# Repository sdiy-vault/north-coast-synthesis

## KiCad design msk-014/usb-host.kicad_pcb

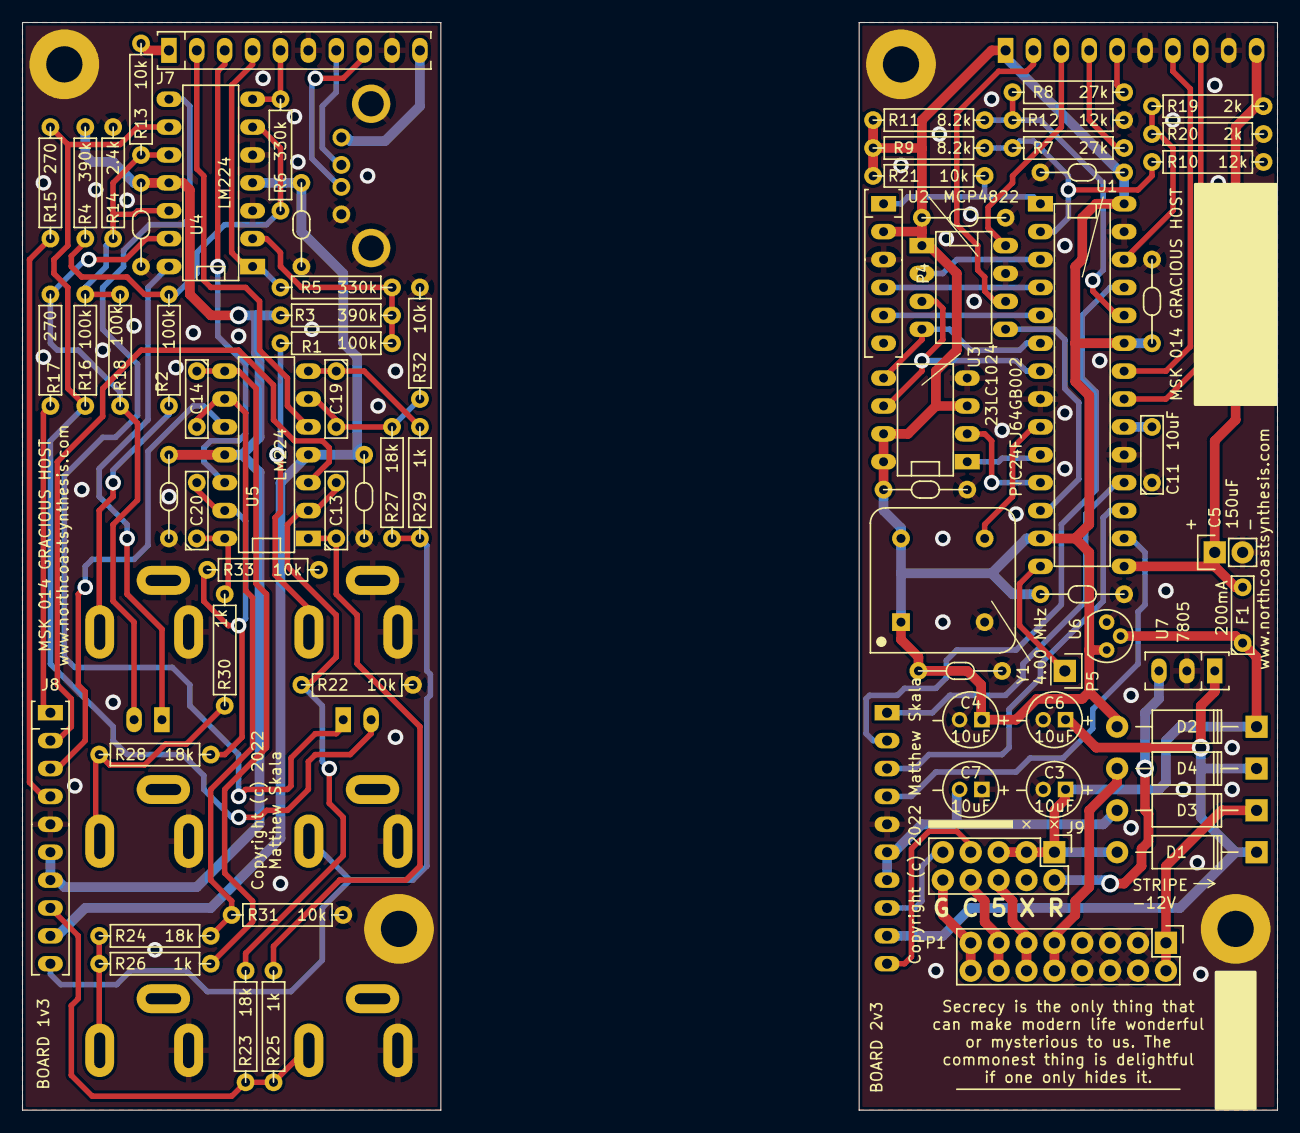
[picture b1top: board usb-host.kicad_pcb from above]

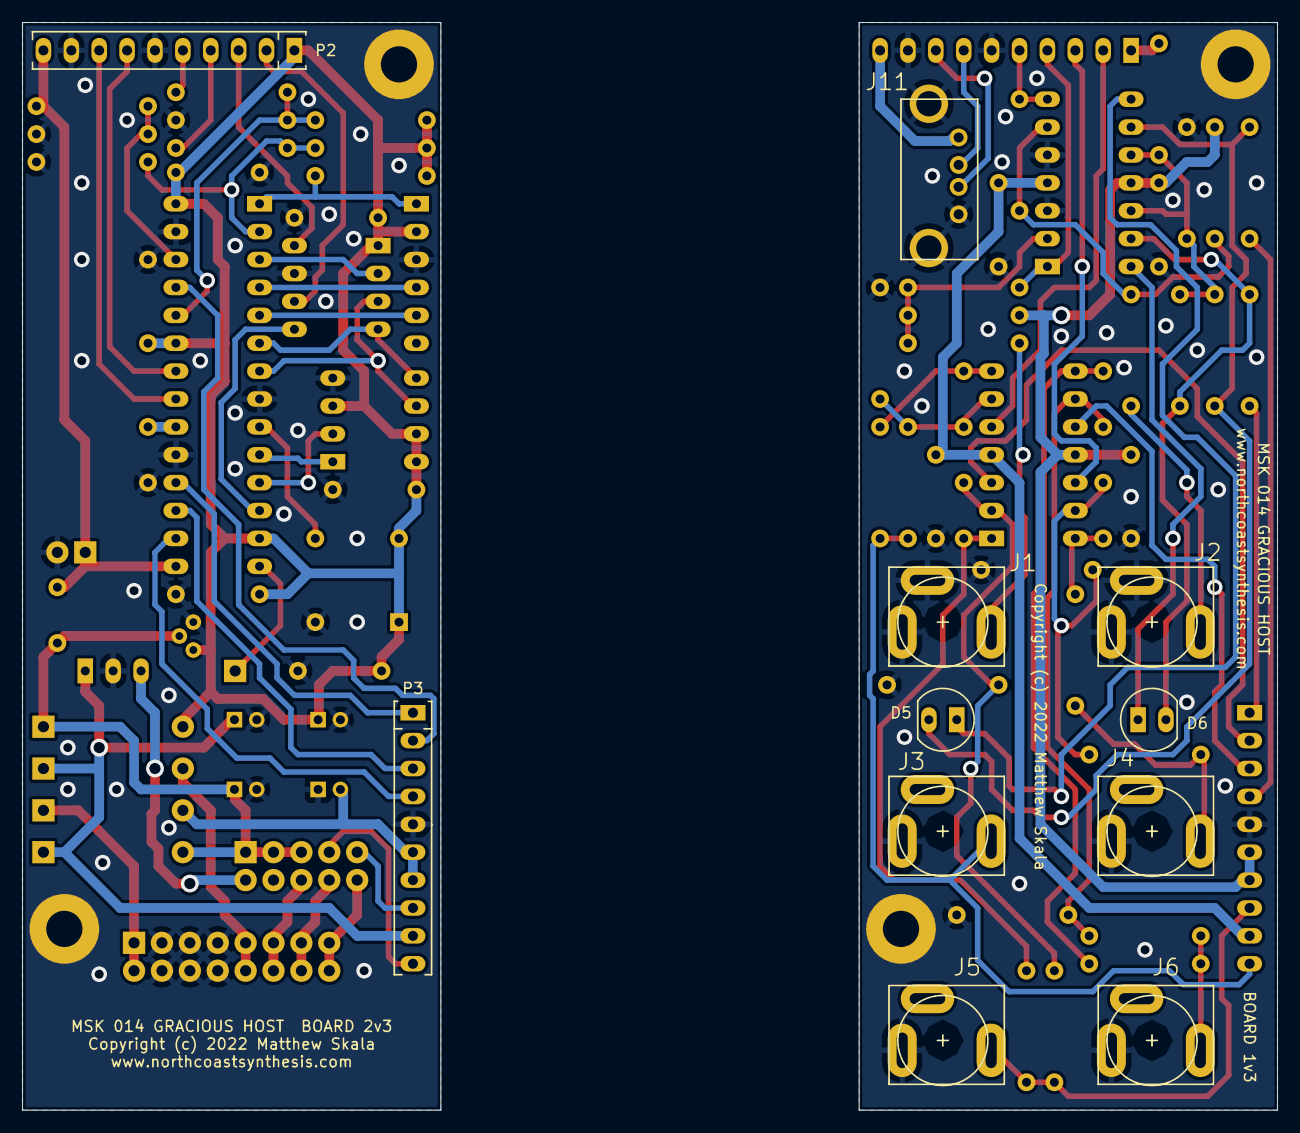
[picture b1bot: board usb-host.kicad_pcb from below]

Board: 2 copper layers, 114.3 x 99.1 mm, 87 parts (11 on the bottom side), 58 nets.

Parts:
C1, C2, C8, C9, C10, C12, C15, C16, C17, C18: 0.1uF; C3msk
C3, C4, C6, C7: 10uF; C08msk
C5: 150uF; 1x02msk
C11: 10uF; C2msk
C13, C14, C19, C20: 100pF; C2msk
D1, D2, D3, D4: 1N5818; DO15msk
D5, D6: MCL056PURGW; LEDmsk
F1: 200mA; C2msk
H1, H2, H3, H4: CONN_01X01; MountingHole_M3
J1, J2, J3, J4, J5, J6: JACK_2P; mono_jack_slotted
J7, J8: CONN_01X10; SIP10-socket
J9: CONN_02X05; 2x05msk
J11: USB_A; USB_A_vert
P1: Conn_02x08_Odd_Even; 2x08ra
P2, P3: CONN_01X10; SIP10-pins
P4: Conn_01x06; SIP6msk
P5: CONN_01X01; 1x01msk
R1, R2, R16, R18: 100k; R4valmsk
R3, R4: 390k; R4valmsk
R5, R6: 330k; R4valmsk
R7, R8: 27k; R4valmsk
R9, R11: 8.2k; R4valmsk
R10, R12: 12k; R4valmsk
R13, R21, R22, R31, R32, R33: 10k; R4valmsk
R14: 2.4k; R4valmsk
R15, R17: 270; R4valmsk
R19, R20: 2k; R4valmsk
R23, R24, R27, R28: 18k; R4valmsk
R25, R26, R29, R30: 1k; R4valmsk
U1: PIC24FJ64GB002; SDIP28_clipped
U2: MCP4822; DIP08msk
U3: 23LC1024; DIP08msk
U4, U5: LM224; DIP14msk_clipped
U6: MCP1700-3302; TO92msk
U7: 7805; SIP3msk
Y1: 4.00 MHz; DIP08_xtal

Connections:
+3.3V: C4.1, C8.2, C9.2, C10.2, C12.2, C15.2, C16.2, D2.1 (A), J7.1, P2.1, P4.2, R9.1, R11.1, R13.1, R21.1, U1.13 (Vdd), U1.23 (Vusb), U1.28 (Vdd), U2.1 (Vdd), U3.3 (SIO2), U3.7 (~HOLD), U3.8 (Vcc), U6.3 (VO), Y1.1 (EN), Y1.8 (Vcc)
+5V: C3.1, D1.1 (A), D2.2 (K), F1.1, J9.1, J9.3, J9.5, U6.2 (VI)
+12V: C2.1, C6.1, C18.1, D1.2 (K), D4.2 (K), J8.9, P3.9, U4.4 (V+), U5.4 (V+), U7.1 (IN)
-12V: C1.1, C7.2, C17.1, D3.1 (A), J8.6, J8.7, P3.6, P3.7, R3.2, R4.2, U4.11 (V-), U5.11 (V-)
/CV1: J7.2, P2.2, U2.6 (VB), U5.5 (+)
/CV2: J7.3, P2.3, U2.8 (VA), U5.12 (+)
/D+: J7.8, J11.3 (D+), P2.8, U1.21 (D+)
/D-: J7.7, J11.2 (D-), P2.7, U1.22 (D-)
/DOUT1: J8.2, P3.2, U1.25 (DOUT1), U5.3 (+)
/DOUT2: J8.3, P3.3, U1.17 (DOUT2), U5.10 (+)
/G1: J5.1, J8.8, J9.9, P3.8, R23.2, R25.2
/LED1: J8.4, P3.4, R15.2, U1.16 (LED1)
/LED2: J8.1, P3.1, R17.2, U1.18 (LED2)
/Vbus: C5.1, F1.2, J7.10, J11.1 (VBUS), P2.10, R19.2, U1.15 (Vbus)
/XCV1: J3.1, J8.10, J9.7, P3.10, R27.2, R29.2
/XIN1: J7.4, P2.4, R5.1, R7.2, U4.1
/XIN2: J7.5, P2.5, R6.1, R8.2, U4.7
GNDREF: C1.2, C2.2, C3.2, C4.2, C5.2, C6.2, C7.1, C8.1, C9.1, C10.1, C11.1, C12.1, C15.1, C16.1, C17.2, C18.2, H1.1, H2.1, H3.1, H4.1, J1.2, J1.3, J2.2, J2.3, J3.3, J4.3, J5.3, J6.3, J7.6, J7.9, J8.5, J11.4 (GND), J11.5 (Shield), P1.3, P1.4, P1.5, P1.6, P1.7, P1.8, P2.6, P2.9, P3.5, P4.3, R10.2, R12.2, R14.2, R20.2, R22.1, R31.1, R32.1, R33.1, U1.8 (Vss), U1.19 (DISVREG), U1.27 (Vss), U2.7 (Vss), U3.4 (Vss), U4.3 (+), U4.5 (+), U6.1 (GND), U7.2 (GND), Y1.4 (GND)
unnamed: C11.2, U1.20 (Vcap)
unnamed: C13.1, R25.1, U5.1
unnamed: C13.2, R22.2, R23.1, U5.2 (-)
unnamed: C14.1, R26.1, U5.8
unnamed: C14.2, R24.1, R31.2, U5.9 (-)
unnamed: C19.1, R29.1, U5.7
unnamed: C19.2, R27.1, R32.2, U5.6 (-)
unnamed: C20.1, R30.1, U5.14
unnamed: C20.2, R28.1, R33.2, U5.13 (-)
unnamed: D3.2 (K), P1.1, P1.2
unnamed: D4.1 (A), P1.9, P1.10
unnamed: D5.1 (A), R15.1, R16.1, U4.9 (-)
unnamed: D5.2 (K), U4.8
unnamed: D6.1 (A), R17.1, R18.1, U4.13 (-)
unnamed: D6.2 (K), U4.14
unnamed: J1.1, R1.2
unnamed: J2.1, R2.2
unnamed: J4.1, R28.2, R30.2
unnamed: J6.1, R24.2, R26.2
unnamed: J9.2, U7.3 (OUT)
unnamed: J9.6, P1.11, P1.12
unnamed: J9.8, P1.13, P1.14
unnamed: J9.10, P1.15, P1.16
unnamed: P4.1, R21.2, U1.1 (~MCLR)
unnamed: P4.4, U1.4 (PGED1)
unnamed: P4.5, U1.5 (PGEC1)
unnamed: P5.1, U1.14 (RB5)
unnamed: R1.1, R3.1, R5.2, U4.2 (-)
unnamed: R2.1, R4.1, R6.2, U4.6 (-)
unnamed: R7.1, R9.2, R10.1, U1.2 (DIN1)
unnamed: R8.1, R11.2, R12.1, U1.24 (DIN2)
unnamed: R13.2, R14.1, R16.2, R18.2, U4.10 (+), U4.12 (+)
unnamed: R19.1, R20.1, U1.26 (AN9)
unnamed: U1.3 (~CS1), U2.2 (~CS)
unnamed: U1.6 (SDO), U2.4 (SDI), U3.5 (SDI)
unnamed: U1.7 (SCK), U2.3 (SCK), U3.6 (SCK)
unnamed: U1.9 (OSCI), Y1.5 (OUT)
unnamed: U1.10 (~CS2), U3.1 (~CS)
unnamed: U1.11 (SDI), U3.2 (SDO)
unnamed: U1.12 (~LDAC), U2.5 (~LDAC)

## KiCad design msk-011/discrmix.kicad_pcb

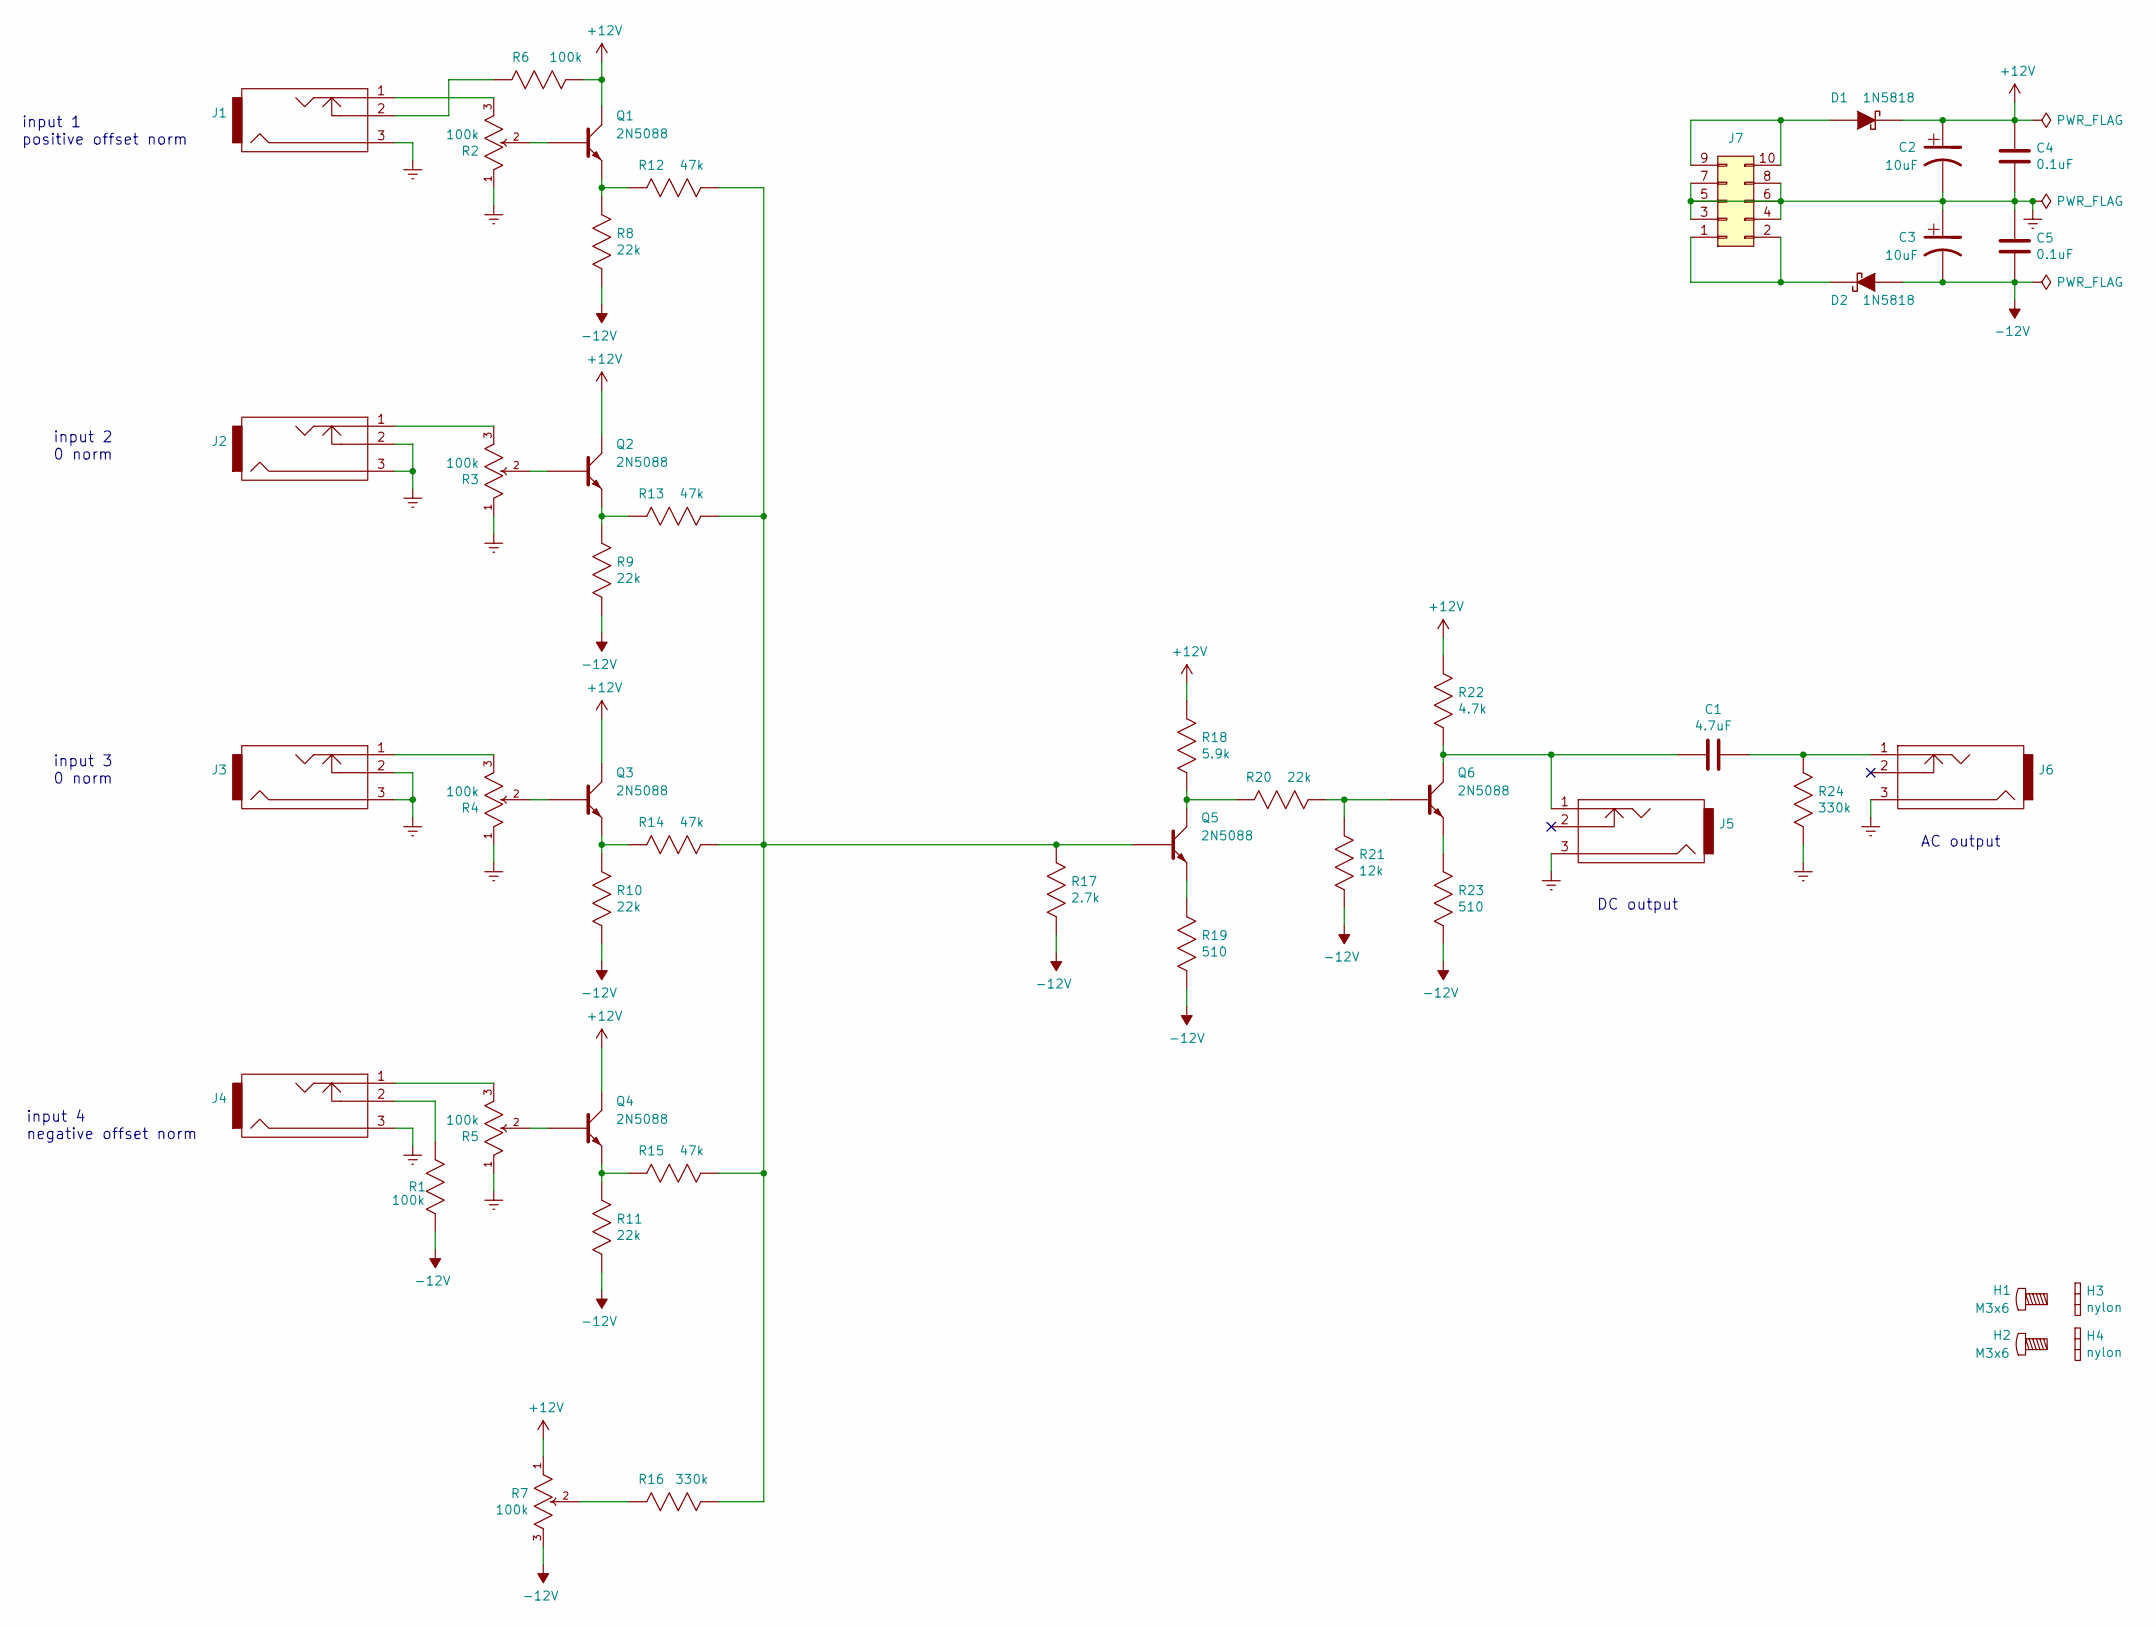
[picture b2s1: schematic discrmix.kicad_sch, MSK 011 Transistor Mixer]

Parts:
C1: 4.7uF; C2_3x2msk
C2, C3: 10uF; C1V7msk
C4, C5: 0.1uF; C3msk
D1, D2: 1N5818; DO15msk
H1, H2: M3x6; Hardware
H3, H4: nylon; Hardware
J1, J2, J3, J4, J5, J6: JACK_2P; jack_ra_slotted_msk
J7: CONN_02X05; 2x05msk
Q1, Q2, Q3, Q4, Q5, Q6: 2N5088; TO92msk
R1, R6: 100k; R4valmsk
R2, R3, R4, R5: 100k; 260Pmsk
R7: 100k; 3386Pmsk
R8, R9, R10, R11, R20: 22k; R4valmsk
R12, R13, R14, R15: 47k; R4valmsk
R16, R24: 330k; R4valmsk
R17: 2.7k; R4valmsk
R18: 5.9k; R4valmsk
R19, R23: 510; R4valmsk
R21: 12k; R4valmsk
R22: 4.7k; R4valmsk

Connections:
+12V: C2.1, C4.1, D1.2 (K), Q1.3 (C), Q2.3 (C), Q3.3 (C), Q4.3 (C), R6.2, R7.1, R18.1, R22.1
-12V: C3.2, C5.2, D2.1 (A), R1.2, R7.3, R8.2, R9.2, R10.2, R11.2, R17.2, R19.2, R21.2, R23.2
GNDREF: C2.2, C3.1, C4.2, C5.1, J1.3, J2.2, J2.3, J3.2, J3.3, J4.3, J5.3, J6.3, J7.3, J7.4, J7.5, J7.6, J7.7, J7.8, R2.1, R3.1, R4.1, R5.1, R24.2
unnamed: C1.1, J6.1, R24.1
unnamed: C1.2, J5.1, Q6.3 (C), R22.2
unnamed: D1.1 (A), J7.9, J7.10
unnamed: D2.2 (K), J7.1, J7.2
unnamed: J1.1, R2.3
unnamed: J1.2, R6.1
unnamed: J2.1, R3.3
unnamed: J3.1, R4.3
unnamed: J4.1, R5.3
unnamed: J4.2, R1.1
unnamed: Q1.1 (E), R8.1, R12.1
unnamed: Q1.2 (B), R2.2
unnamed: Q2.1 (E), R9.1, R13.1
unnamed: Q2.2 (B), R3.2
unnamed: Q3.1 (E), R10.1, R14.1
unnamed: Q3.2 (B), R4.2
unnamed: Q4.1 (E), R11.1, R15.1
unnamed: Q4.2 (B), R5.2
unnamed: Q5.1 (E), R19.1
unnamed: Q5.2 (B), R12.2, R13.2, R14.2, R15.2, R16.2, R17.1
unnamed: Q5.3 (C), R18.2, R20.1
unnamed: Q6.1 (E), R23.1
unnamed: Q6.2 (B), R20.2, R21.1
unnamed: R7.2, R16.1

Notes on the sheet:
DC output
AC output
input 3 0 norm
input 1 positive offset norm
input 4 negative offset norm
input 2 0 norm

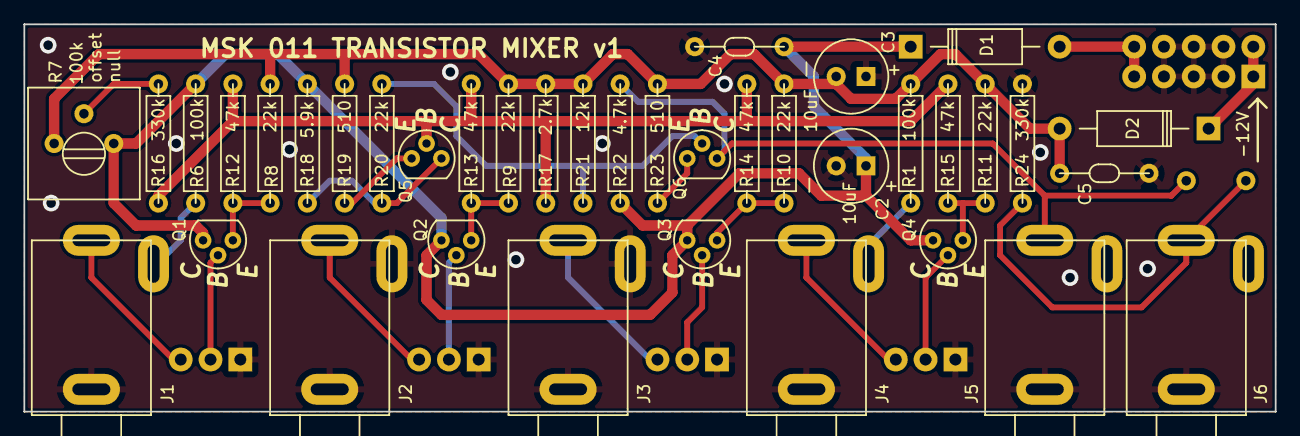
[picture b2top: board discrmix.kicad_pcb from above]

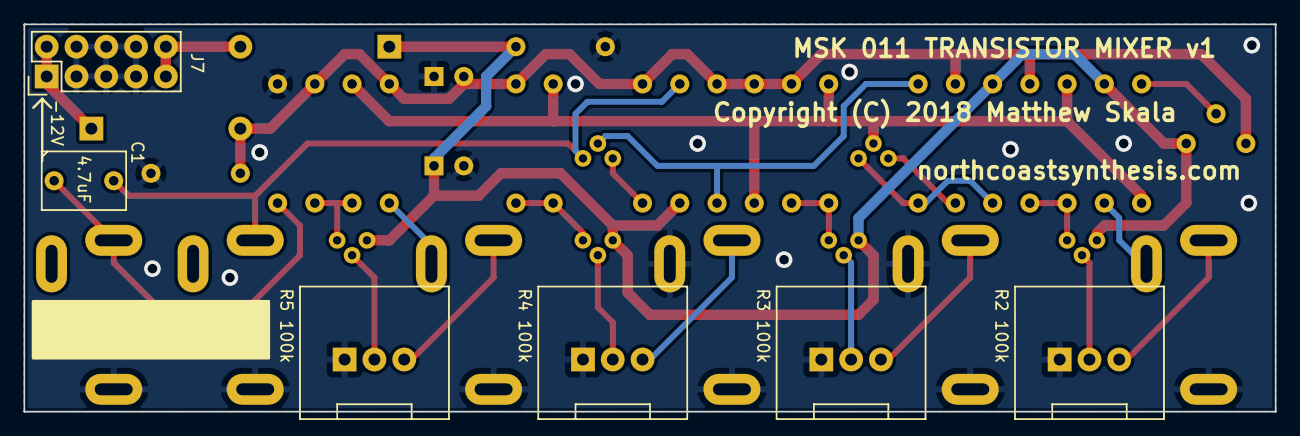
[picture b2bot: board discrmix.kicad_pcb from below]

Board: 2 copper layers, 106.7 x 33.0 mm, 44 parts (6 on the bottom side), 27 nets.

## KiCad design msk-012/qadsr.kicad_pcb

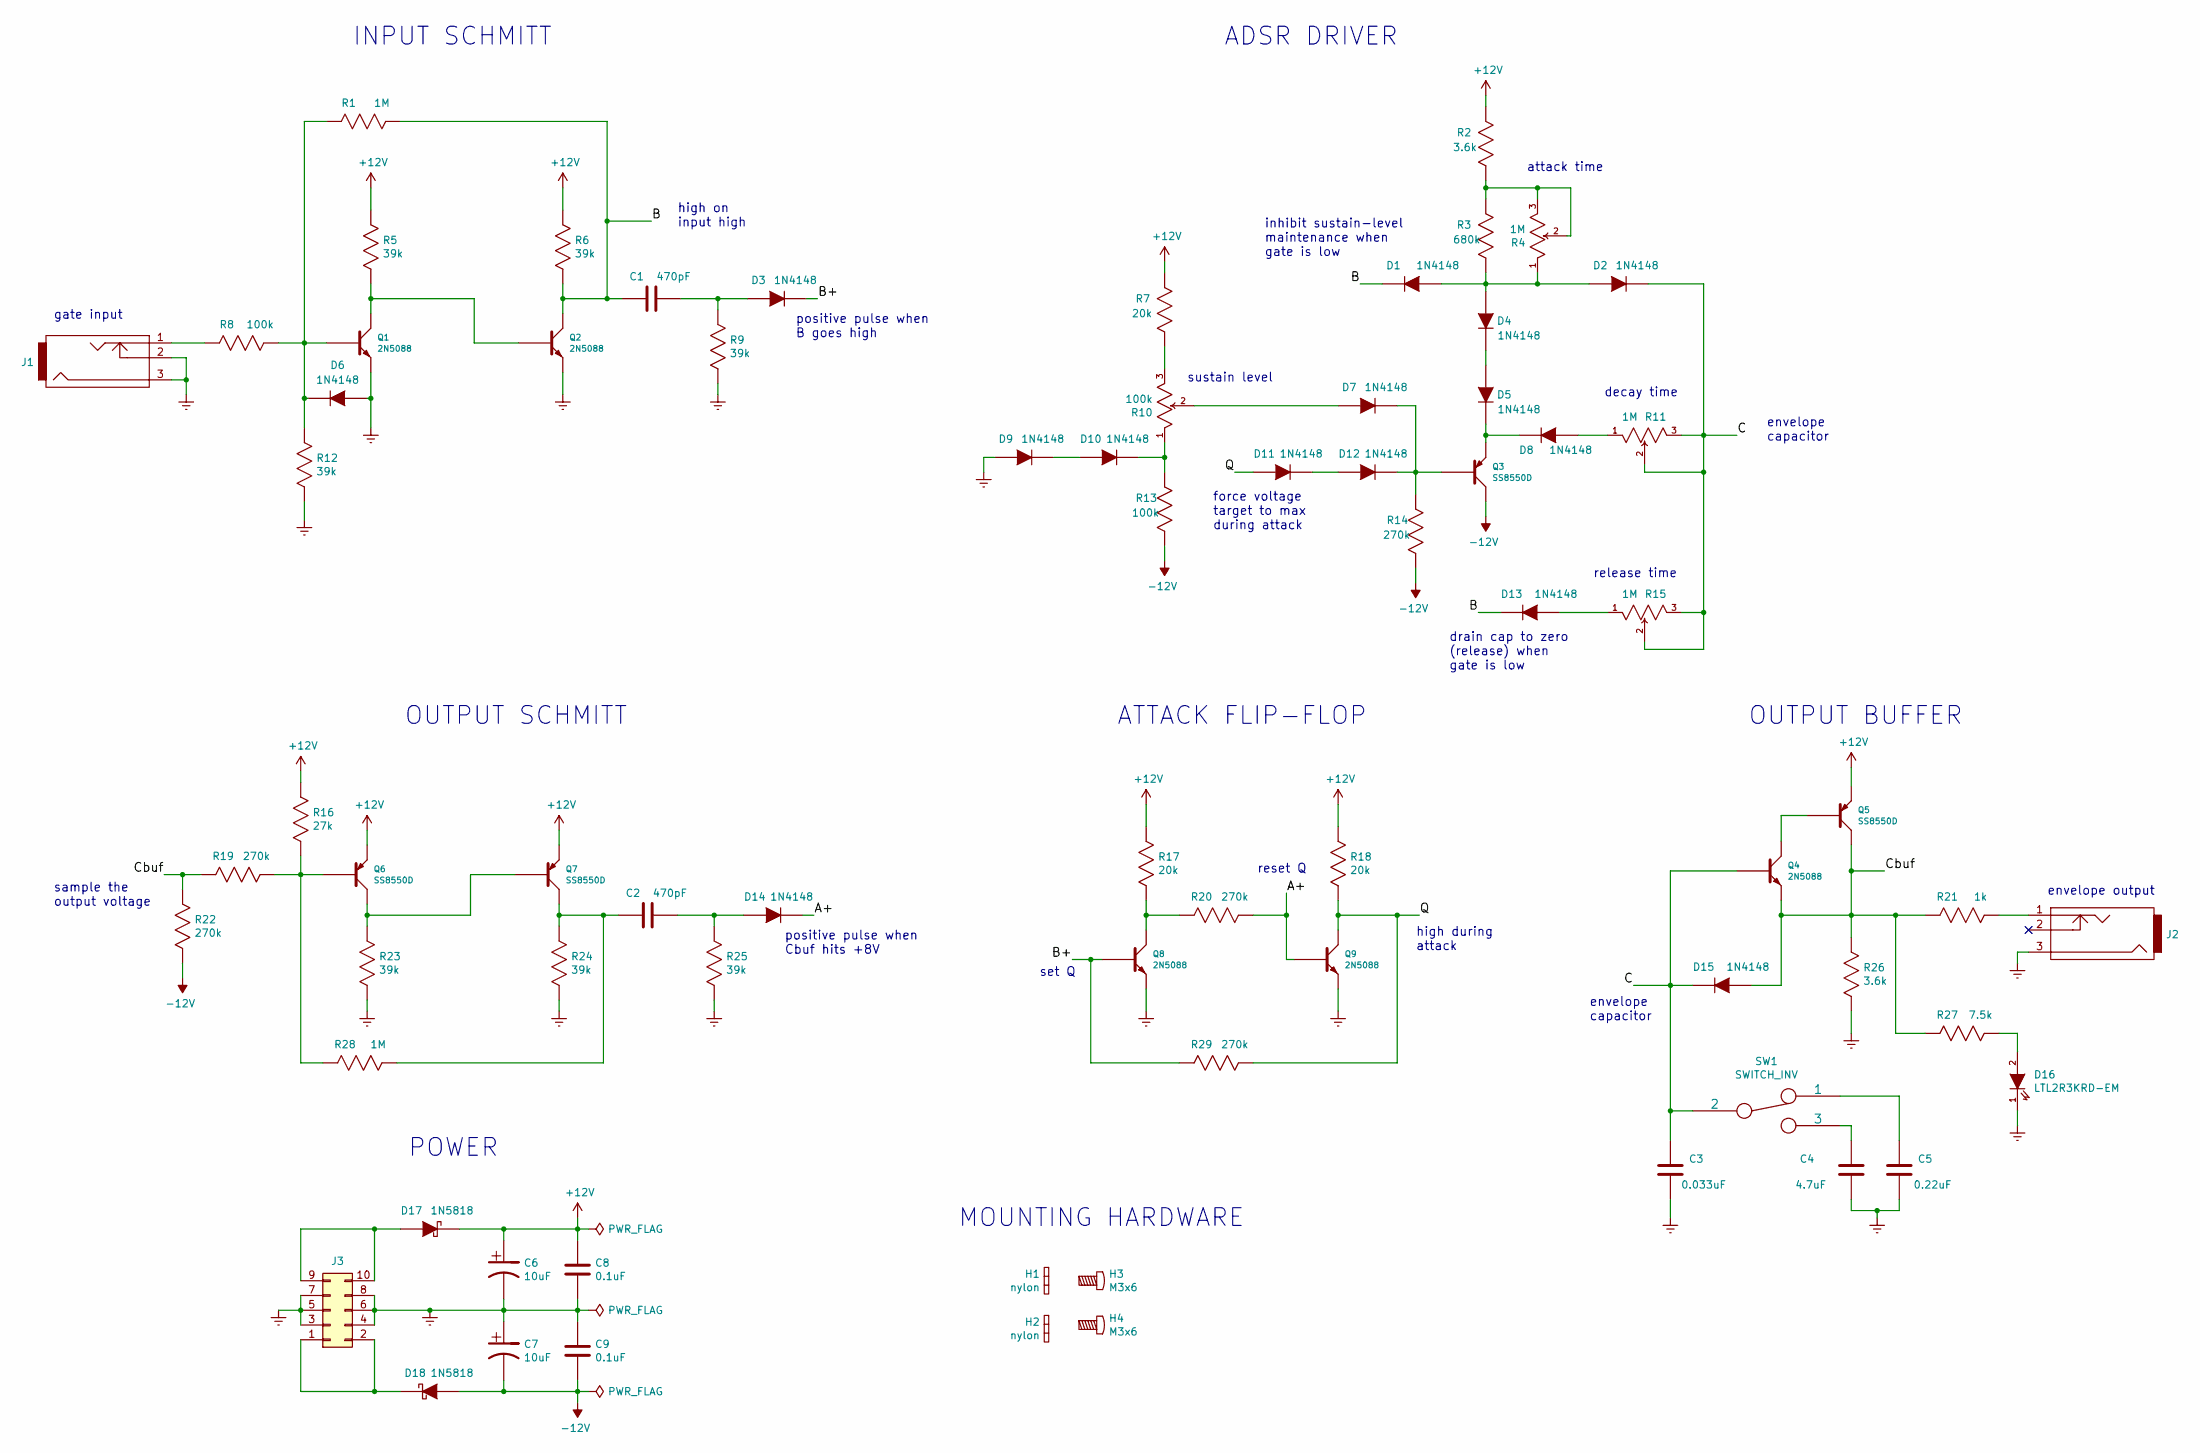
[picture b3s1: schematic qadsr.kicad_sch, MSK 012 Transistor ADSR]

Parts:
C1, C2: 470pF; C2msk
C3: 0.033uF; C2msk
C4: 4.7uF; C2_3x2msk
C5: 0.22uF; C2msk
C6, C7: 10uF; C1V7msk
C8, C9: 0.1uF; C3msk
D1, D2, D3, D4, D5, D6, D7, D8, D9, D10, D11, D12, D13, D14, D15: 1N4148; DO35_3msk
D16: LTL2R3KRD-EM; 1x02msk
D17, D18: 1N5818; DO15msk
H1, H2: nylon; Hardware
H3, H4: M3x6; Hardware
J1, J2: JACK_2P; jack_ra_slotted_msk
J3: CONN_02X05; 2x05msk
Q1, Q2, Q4, Q8, Q9: 2N5088; TO92msk
Q3, Q5, Q6, Q7: SS8550D; TO92Xmsk
R1, R28: 1M; R35valmsk
R2, R26: 3.6k; R35valmsk
R3: 680k; R35valmsk
R4, R11, R15: 1M; P160KNPpot
R5, R6, R9, R12, R23, R24, R25: 39k; R35valmsk
R7, R17, R18: 20k; R35valmsk
R8, R13: 100k; R35valmsk
R10: 100k; P160KNPpot
R14, R19, R20, R22, R29: 270k; R35valmsk
R16: 27k; R35valmsk
R21: 1k; R35valmsk
R27: 7.5k; R35valmsk
SW1: SWITCH_INV; 1x03msk

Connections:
+12V: C6.1, C8.1, D17.2 (K), Q5.1 (E), Q6.1 (E), Q7.1 (E), R2.1, R5.1, R6.1, R7.1, R16.1, R17.1, R18.1
-12V: C7.2, C9.2, D18.1 (A), Q3.3 (C), R13.2, R14.2, R22.2
/A+: D14.2 (K), Q9.2 (B), R20.2
/B: C1.1, D1.2 (K), D13.2 (K), Q2.3 (C), R1.2, R6.2
/B+: D3.2 (K), Q8.2 (B), R29.1
/C: C3.1, D2.2 (K), D15.2 (K), Q4.2 (B), R11.2, R11.3, R15.2, R15.3, SW1.2
/Cbuf: D15.1 (A), Q4.1 (E), Q5.3 (C), R19.1, R21.1, R22.1, R26.1, R27.1
/Q: D11.1 (A), Q9.3 (C), R18.2, R29.2
GNDREF: C3.2, C4.2, C5.2, C6.2, C7.1, C8.2, C9.1, D6.1 (A), D9.1 (A), D16.1 (A), J1.2, J1.3, J2.3, J3.3, J3.4, J3.5, J3.6, J3.7, J3.8, Q1.1 (E), Q2.1 (E), Q8.1 (E), Q9.1 (E), R9.2, R12.2, R23.2, R24.2, R25.2, R26.2
unnamed: C1.2, D3.1 (A), R9.1
unnamed: C2.1, Q7.3 (C), R24.1, R28.2
unnamed: C2.2, D14.1 (A), R25.1
unnamed: C4.1, SW1.3
unnamed: C5.1, SW1.1
unnamed: D1.1 (A), D2.1 (A), D4.1 (A), R3.2, R4.1
unnamed: D4.2 (K), D5.1 (A)
unnamed: D5.2 (K), D8.2 (K), Q3.1 (E)
unnamed: D6.2 (K), Q1.2 (B), R1.1, R8.2, R12.1
unnamed: D7.1 (A), R10.2
unnamed: D8.1 (A), R11.1
unnamed: D9.2 (K), D10.1 (A)
unnamed: D10.2 (K), R10.1, R13.1
unnamed: D11.2 (K), D12.1 (A)
unnamed: D7.2 (K), D12.2 (K), Q3.2 (B), R14.1
unnamed: D13.1 (A), R15.1
unnamed: D16.2 (K), R27.2
unnamed: D17.1 (A), J3.9, J3.10
unnamed: D18.2 (K), J3.1, J3.2
unnamed: J1.1, R8.1
unnamed: J2.1, R21.2
unnamed: Q1.3 (C), Q2.2 (B), R5.2
unnamed: Q4.3 (C), Q5.2 (B)
unnamed: Q6.2 (B), R16.2, R19.2, R28.1
unnamed: Q6.3 (C), Q7.2 (B), R23.1
unnamed: Q8.3 (C), R17.2, R20.1
unnamed: R2.2, R3.1, R4.2, R4.3
unnamed: R7.2, R10.3

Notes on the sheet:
inhibit sustain-level maintenance when gate is low
drain cap to zero (release) when gate is low
positive pulse when B goes high
ADSR DRIVER
sustain level
envelope output
POWER
OUTPUT SCHMITT
decay time
set Q
envelope capacitor
OUTPUT BUFFER
reset Q
attack time
sample the output voltage
MOUNTING HARDWARE
ATTACK FLIP-FLOP
positive pulse when Cbuf hits +8V
INPUT SCHMITT
force voltage target to max during attack
release time
high during attack
high on input high
gate input

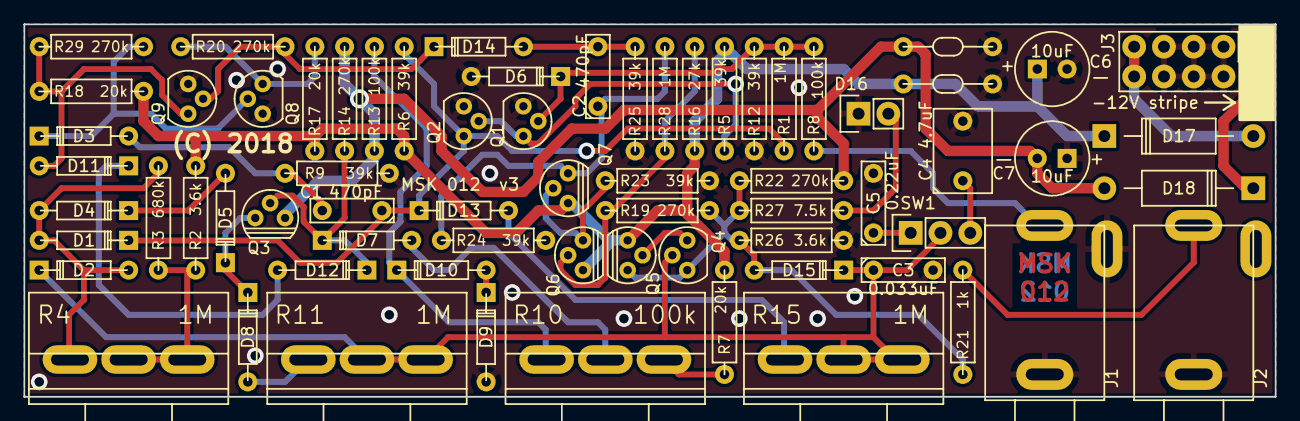
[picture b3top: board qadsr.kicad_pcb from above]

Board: 2 copper layers, 106.7 x 31.8 mm, 69 parts (0 on the bottom side), 37 nets.

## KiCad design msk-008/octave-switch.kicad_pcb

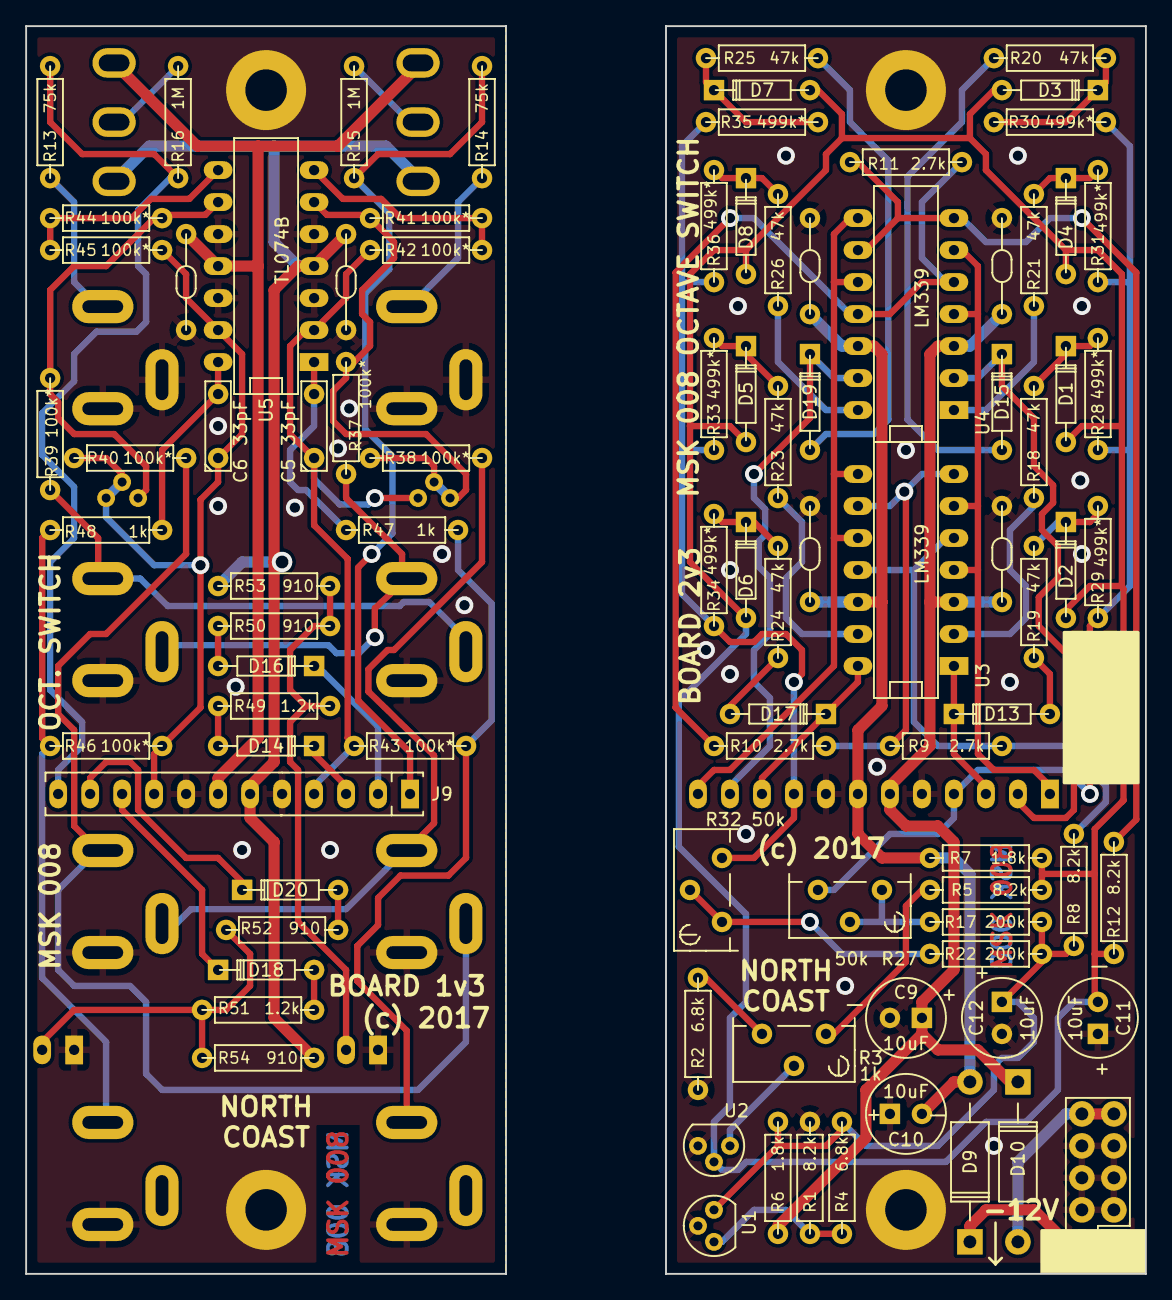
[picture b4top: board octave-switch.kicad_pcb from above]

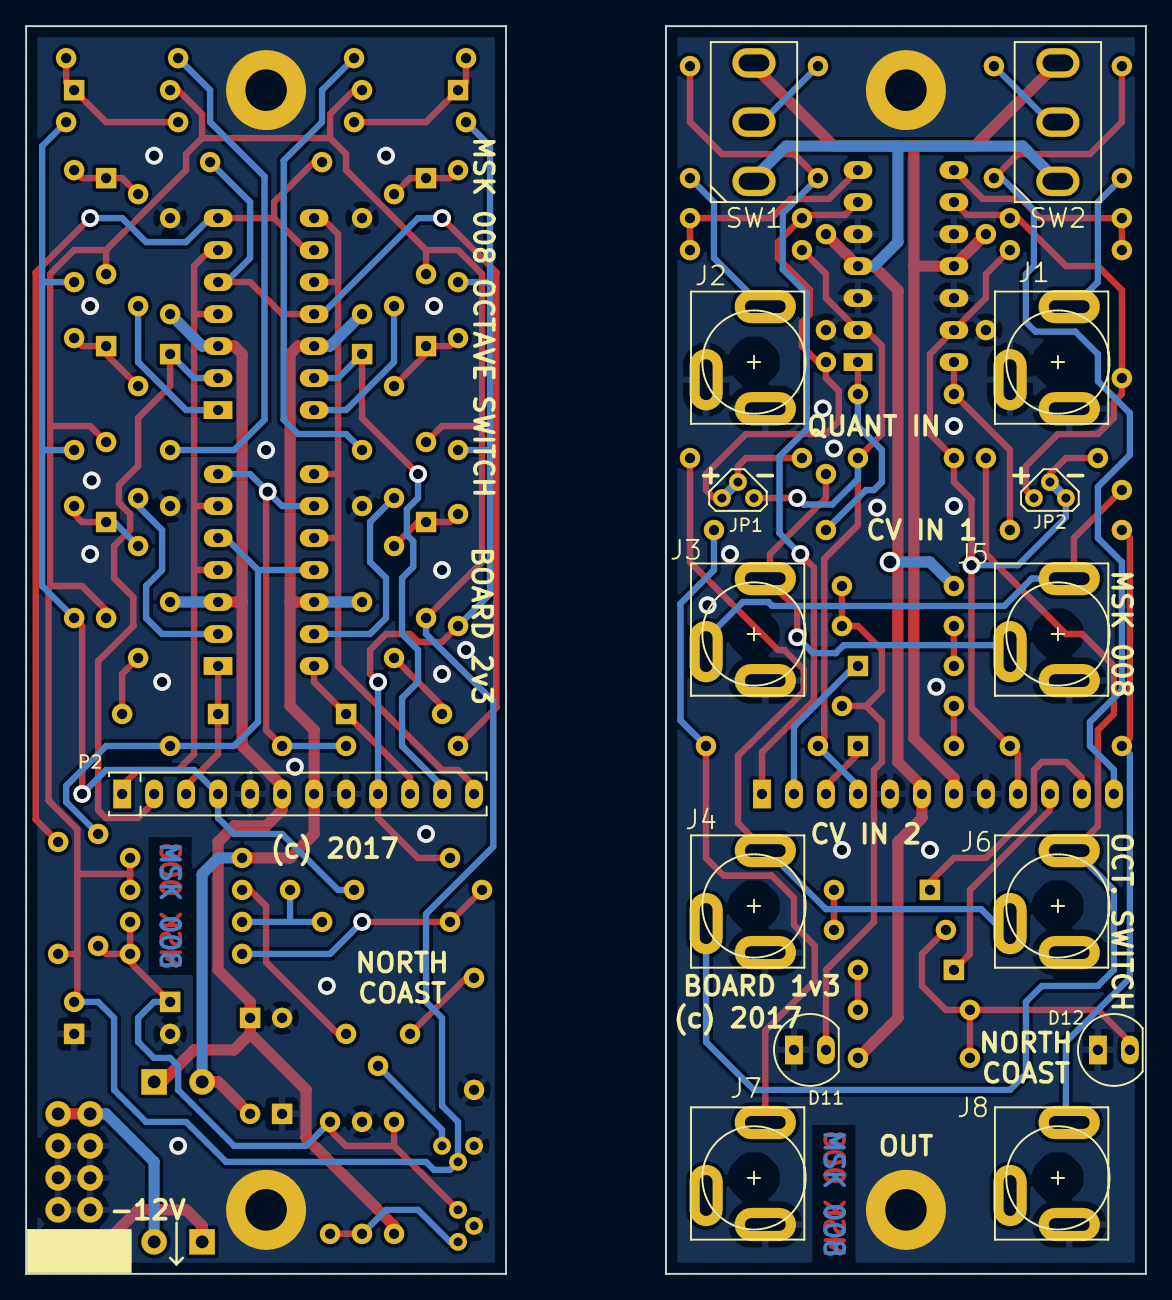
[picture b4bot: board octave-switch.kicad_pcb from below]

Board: 2 copper layers, 88.9 x 99.1 mm, 110 parts (15 on the bottom side), 65 nets.

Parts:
C1, C2, C3, C4, C7, C8: 0.1uF; C3msk
C5, C6: 33pF; C2msk
C9, C10, C11, C12: 10uF; C1V7msk
D1, D2, D3, D4, D5, D6, D7, D8, D13, D14, D15, D16, D17, D18, D19, D20: 1N4148; DO35_3msk
D9, D10: 1N5818; DO15msk
D11, D12: MCL056PURGW; LEDmsk
H1, H2, H3, H4: CONN_01X01; MountingHole_M3
J1, J2, J3, J4, J5, J6, J7, J8: JACK_2P; mono_jack_slotted
J9: CONN_01X12; SIP12msk
JP1: SWITCH_INV; SPDTjleft
JP2: SWITCH_INV; SPDTjright
P1: CONN_02X05; 2x05msk
P2: CONN_01X12; SIP12msk
R1, R5, R8, R12: 8.2k; R35valmsk
R2, R4: 6.8k; R35valmsk
R3: 1k; 3296Ymsk
R6, R7: 1.8k; R35valmsk
R9, R10, R11: 2.7k; R35valmsk
R13, R14: 75k; R35valmsk
R15, R16: 1M; R35valmsk
R17, R22: 200k; R35valmsk
R18, R19, R20, R21, R23, R24, R25, R26: 47k; R35valmsk
R27, R32: 50k; 3296Ymsk
R28, R29, R30, R31, R33, R34, R35, R36: 499k*; R35valmsk
R37, R38, R39, R40, R41, R42, R43, R44, R45, R46: 100k*; R35valmsk
R47, R48: 1k; R35valmsk
R49, R51: 1.2k; R35valmsk
R50, R52, R53, R54: 910; R35valmsk
SW1, SW2: 100SP3T1B1M1QEH; ESwitch100SP
U1, U2: TL431; TO92msk
U3, U4: LM339; DIP14msk
U5: TL074B; DIP14msk

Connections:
+12V: C1.2, C2.2, C7.1, C9.1, D10.2 (K), J9.6, P2.6, R6.1, R53.2, R54.2, SW1.1, SW2.1, U3.3 (V+), U4.3 (V+), U5.4 (V+)
-12V: C3.2, C4.2, C8.1, C10.2, D9.1 (A), J9.7, P2.7, R7.2, SW1.3, SW2.3, U3.12 (GND), U4.12 (GND), U5.11 (V-)
/CVA: J9.1, P2.1, R14.2, R15.1, U3.4 (-), U3.6 (-), U4.4 (-), U4.6 (-)
/CVB: J9.12, P2.12, R13.2, R16.1, U3.8 (-), U3.10 (-), U4.8 (-), U4.10 (-)
/LEDAX: D13.2 (K), D14.2 (K), J9.3, P2.3, U3.1
/LEDAY: D15.2 (K), D16.2 (K), J9.2, P2.2, U4.2
/LEDBX: D17.2 (K), D18.2 (K), J9.10, P2.10, U3.14
/LEDBY: D19.2 (K), D20.2 (K), J9.11, P2.11, U4.13
/OUTA: C5.1, J9.4, JP1.3, P2.4, R27.3, R28.2, R29.2, R30.2, R31.2, R42.1, R43.1, U5.2 (-)
/OUTB: C6.1, J9.9, JP2.1, P2.9, R32.3, R33.2, R34.2, R35.2, R36.2, R45.1, R46.1, U5.13 (-)
GNDREF: C1.1, C2.1, C3.1, C4.1, C7.2, C8.2, C9.2, C10.1, C11.1, C12.2, D11.2 (K), D12.2 (K), H1.1, H2.1, H3.1, H4.1, J1.2, J1.3, J2.2, J2.3, J3.3, J4.3, J5.3, J6.3, J7.3, J8.3, J9.5, J9.8, P1.3, P1.4, P1.5, P1.6, P1.7, P1.8, P2.5, P2.8, R1.2, R2.1, U1.2 (A), U2.3 (K), U5.3 (+), U5.5 (+), U5.10 (+), U5.12 (+)
unnamed: C5.2, R47.1, U5.1
unnamed: C6.2, R48.1, U5.14
unnamed: C11.2, D1.1 (A), D2.1 (A), D3.1 (A), D4.1 (A), D5.1 (A), D6.1 (A), D7.1 (A), D8.1 (A), R5.2, R7.1, R12.2, U2.2 (A)
unnamed: C12.1, R4.2, R6.2, R8.1, R17.1, R22.1, U1.3 (K)
unnamed: D1.2 (K), R18.2, R28.1
unnamed: D2.2 (K), R19.2, R29.1
unnamed: D3.2 (K), R20.2, R30.1
unnamed: D4.2 (K), R21.2, R31.1
unnamed: D5.2 (K), R23.2, R33.1
unnamed: D6.2 (K), R24.2, R34.1
unnamed: D7.2 (K), R25.2, R35.1
unnamed: D8.2 (K), R26.2, R36.1
unnamed: D9.2 (K), P1.1, P1.2
unnamed: D10.1 (A), P1.9, P1.10
unnamed: D11.1 (A), R49.2, R50.2, R53.1
unnamed: D12.1 (A), R51.2, R52.2, R54.1
unnamed: D13.1 (A), R19.1
unnamed: D14.1 (A), R49.1
unnamed: D15.1 (A), R20.1
unnamed: D16.1 (A), R50.1
unnamed: D17.1 (A), R24.1
unnamed: D18.1 (A), R51.1
unnamed: D19.1 (A), R25.1
unnamed: D20.1 (A), R52.1
unnamed: J1.1, R13.1
unnamed: J2.1, R14.1
unnamed: J3.1, J5.2, R37.1
unnamed: J3.2, J5.1, R39.1
unnamed: J4.1, J6.2, R38.1
unnamed: J4.2, J6.1, R40.1
unnamed: J7.1, R43.2, R47.2
unnamed: J8.1, R46.2, R48.2
unnamed: JP1.1, R37.2, R41.1, U5.6 (-)
unnamed: JP1.2, R38.2
unnamed: JP2.2, R40.2
unnamed: JP2.3, R39.2, R44.1, U5.9 (-)
unnamed: R1.1, R4.1, U1.1 (R)
unnamed: R2.2, R3.3
unnamed: R3.1, R5.1
unnamed: R3.2, U2.1 (R)
unnamed: R8.2, R9.1, U3.5 (+), U3.11 (+)
unnamed: R9.2, R10.1, U3.7 (+), U3.9 (+)
unnamed: R10.2, R11.1, U4.5 (+), U4.11 (+)
unnamed: R11.2, R12.1, U4.7 (+), U4.9 (+)
unnamed: R15.2, SW1.2
unnamed: R16.2, SW2.2
unnamed: R17.2, R27.1, R27.2
unnamed: R18.1, U3.2
unnamed: R21.1, U4.1
unnamed: R22.2, R32.1, R32.2
unnamed: R23.1, U3.13
unnamed: R26.1, U4.14
unnamed: R41.2, R42.2, U5.7
unnamed: R44.2, R45.2, U5.8

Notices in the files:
msk-008/octave-switch.kicad_pcb:
(c) 2017
msk-009/coiler.kicad_pcb:
(c) 2018-2020
Copyright (c) 2018-2020 Matthew Skala
msk-010/manysine.kicad_pcb:
Copyright (C) 2017 Matthew Skala
msk-011/discrmix.kicad_pcb:
Copyright (C) 2018 Matthew Skala
msk-012/qadsr.kicad_pcb:
Transistor ADSR (C) 2018
(C) 2018
msk-014/usb-host.kicad_pcb:
Copyright (c) 2022 Matthew Skala
